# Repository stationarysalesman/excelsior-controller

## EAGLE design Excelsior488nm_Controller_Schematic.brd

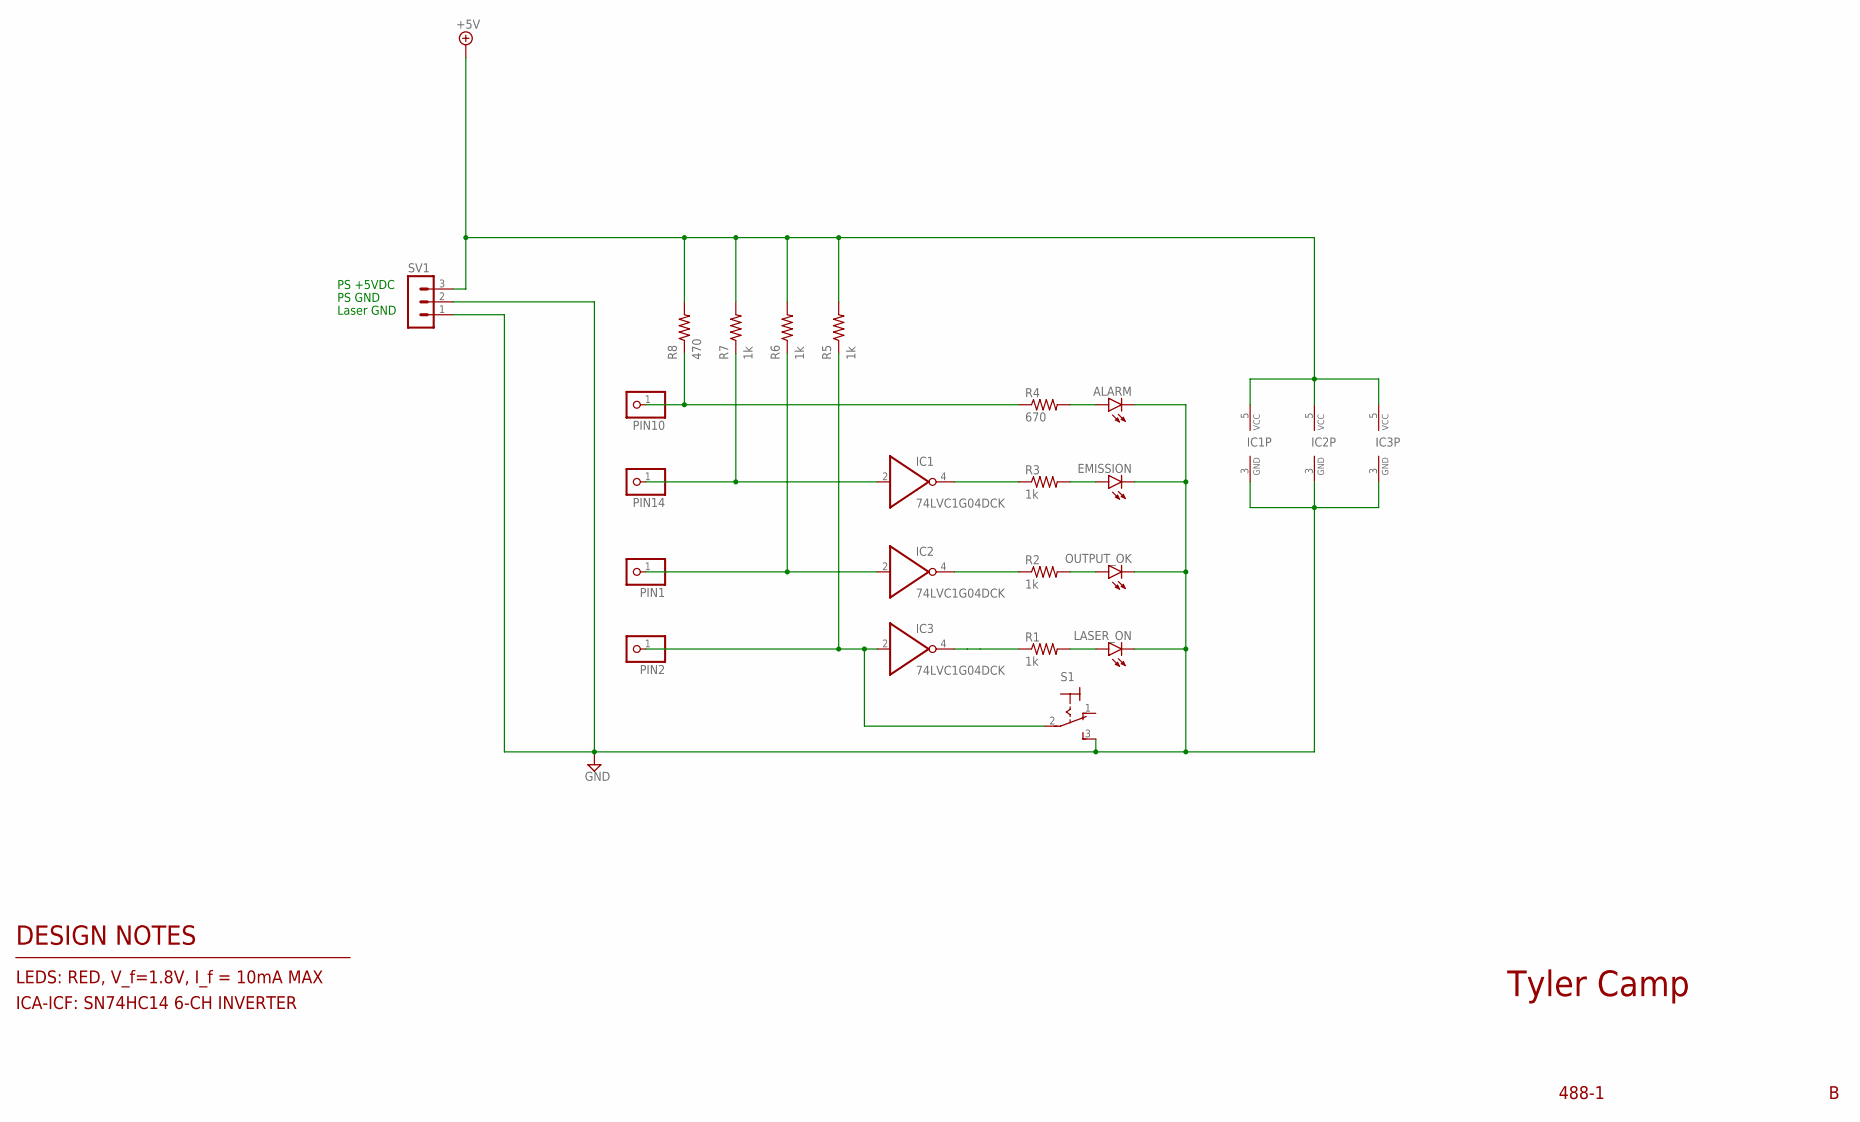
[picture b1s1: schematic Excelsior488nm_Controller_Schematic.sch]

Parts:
ALARM: LED3MM
EMISSION: LED3MM
IC1, IC2, IC3: 74LVC1G04DCK; SC70-5
LASER_ON: LED3MM
OUTPUT_OK: LED3MM
PIN1, PIN2, PIN10, PIN14: PINHD-1X1; 1X01
R1, R2, R3, R5, R6, R7: 1k; R0603
R4: 670; R0603
R8: 470; R0603
S1: M9040P
SV1: MA03-1

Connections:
+5V: IC1.5 (VCC), IC2.5 (VCC), IC3.5 (VCC), R5.2, R6.2, R7.2, R8.2, SV1.3
GND: ALARM.K (C), EMISSION.K (C), IC1.3 (GND), IC2.3 (GND), IC3.3 (GND), LASER_ON.K (C), OUTPUT_OK.K (C), S1.3 (S), SV1.1, SV1.2
unnamed: IC1.4 (O), R3.1
unnamed: IC1.2 (I), PIN14.1, R7.1
unnamed: IC2.2 (I), PIN1.1, R6.1
unnamed: LASER_ON.A, R1.2
unnamed: IC3.4 (O), R1.1
unnamed: IC2.4 (O), R2.1
unnamed: PIN10.1, R4.1, R8.1
unnamed: ALARM.A, R4.2
unnamed: EMISSION.A, R3.2
unnamed: OUTPUT_OK.A, R2.2
PIN2: IC3.2 (I), PIN2.1, R5.1, S1.2

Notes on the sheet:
Laser GND
PS GND
PS +5VDC
Tyler Camp
LEDS: RED, V_f=1.8V, I_f = 10mA MAX
ICA-ICF: SN74HC14 6-CH INVERTER
DESIGN NOTES
488-1

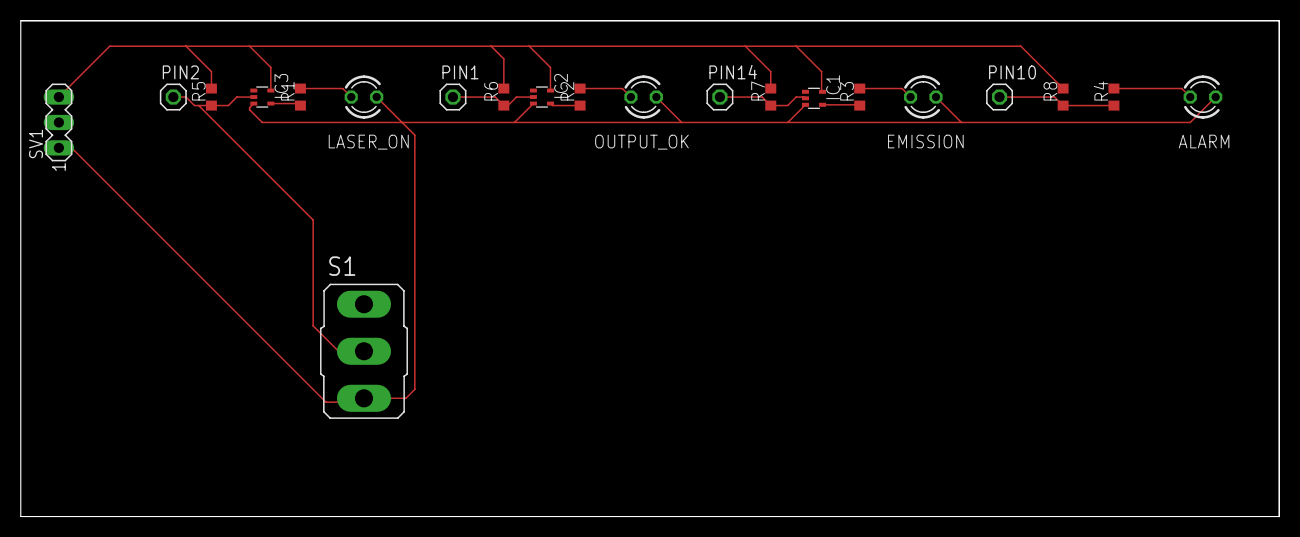
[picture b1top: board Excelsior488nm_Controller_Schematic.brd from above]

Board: 2 copper layers, 125.7 x 49.5 mm, 21 parts (0 on the bottom side), 13 nets.

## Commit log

2019-07-13 Finalized 488-1A
2019-07-15 Revision B
2019-07-15 Schematic update
2019-07-16 Board layout
